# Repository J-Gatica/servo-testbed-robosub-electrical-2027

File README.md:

# Servo Testbed Project

Team members:
- Jayden
- Aleks
- Dwayne
- Cason

# Project Overview

Design and print a PCB to test the functionality of different types of servos for the SDSU Mechatronics Club during the 2026 Fall semester
- "create a pcb board that outputs a pwm signal that has .5-2.5ms high period (just like intro project) that is manually controlled by potentiometer"

PCB schematic and layout designed using KiCAD V10.0

MCU programmed using STM32CubeIDE in C

# Capabilities

- STM32F103C8T6 controlled

- Testing mode control:
  - Manual potentiometer sweep
  - Automatic sweep, potentiometer speed control
  - X degree step increment, potentiometer speed control
  - WIP
  
- 12V, 8.4V, 7.4V, 6V, 5V, 3V3 voltage outputs
  - 3/4 of each, two 12V outputs. 16/22 outputs total
  - reverse polarity protection up to (insert pmos ratings)

- Status display
  - Current draw
  - Expected output angle
  - Potentiometer angle
  - PWM data (duty cycle, frequency)

- 2 DC motor outputs
  - CAN control

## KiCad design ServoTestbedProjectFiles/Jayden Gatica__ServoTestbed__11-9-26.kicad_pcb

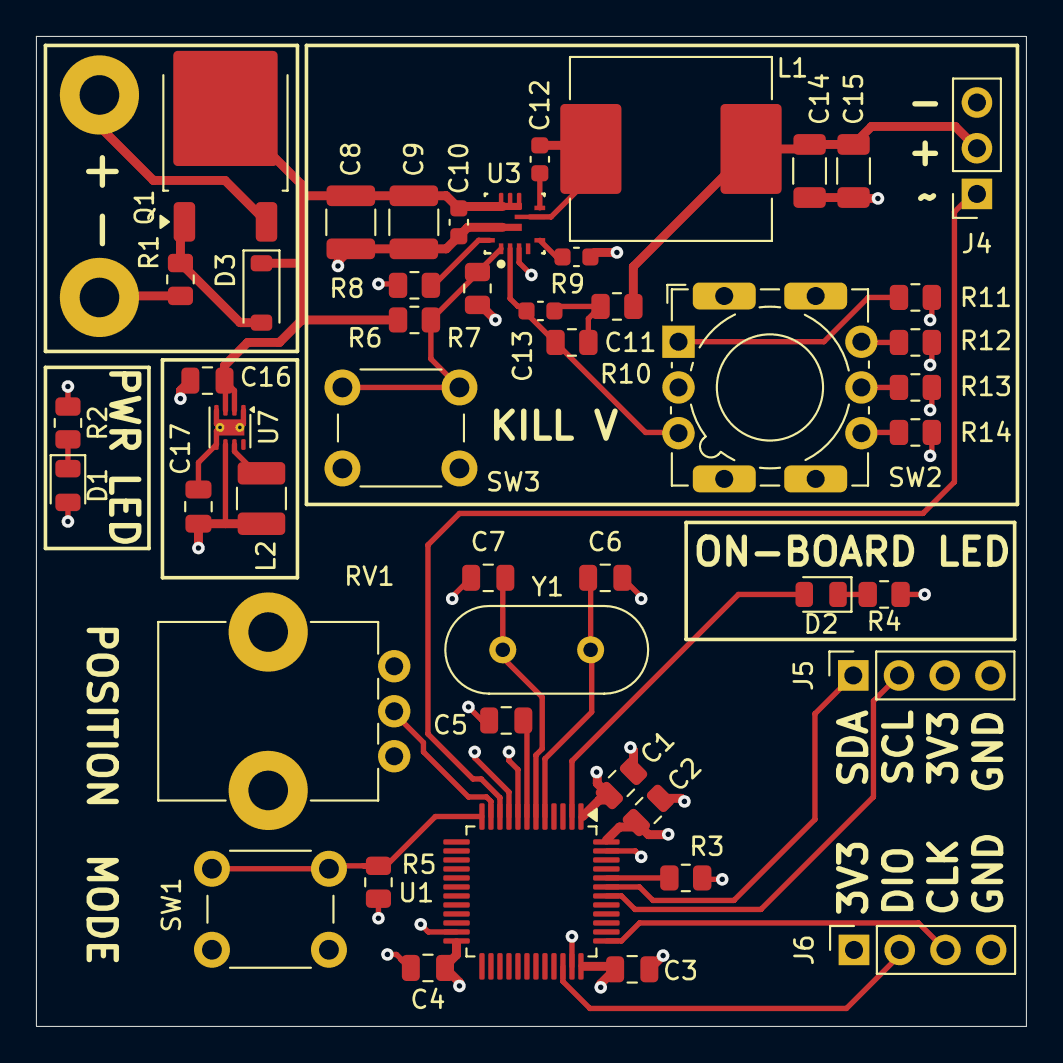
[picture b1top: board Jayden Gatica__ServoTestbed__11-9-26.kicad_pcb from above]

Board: 4 copper layers, 55.0 x 55.0 mm, 50 parts (0 on the bottom side), 32 nets.

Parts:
+: INPUT +15V; MountingHole_2.2mm_M2_Pad
-: INPUT GND; MountingHole_2.2mm_M2_Pad
C1, C2, C3, C4: 100nF; C_0805_2012Metric
C5: 100n; C_0805_2012Metric
C6: 30pF; C_0805_2012Metric
C7: 30Pf; C_0805_2012Metric
C8, C9: 10uF; C_1210_3225Metric
C10, C12: 0.1uF; C_0603_1608Metric
C11: 47nF; C_0603_1608Metric
C13: 150pF; C_0603_1608Metric
C14, C15: 22uF; C_1206_3216Metric
C16: 10uF; C_0805_2012Metric
C17: 22uF; C_0805_2012Metric
D1: PWR LED; LED_0805_2012Metric
D2: On-Board LED; LED_0805_2012Metric
D3: BZT52C12 - 12V; D_SOD-123
J4: 12V servo; PinSocket_1x03_P2.54mm_Vertical
J5: I2C display connector; PinSocket_1x04_P2.54mm_Vertical
J6: ST-link connector; PinSocket_1x04_P2.54mm_Vertical
L1: 5.6 uH; L_Bourns_SRP1050WA
L2: 2.2uH; L_1210_3225Metric
Q1: AO34185e; TO-252-2
R1: 100k; R_0805_2012Metric
R2, R4: 510R; R_0805_2012Metric
R3, R5: 10k; R_0805_2012Metric
R6: 169k; R_0805_2012Metric
R7: 36.1k; R_0805_2012Metric
R8: 52.3k; R_0805_2012Metric
R9: 49.9; R_0805_2012Metric
R10: 73.2K; R_0805_2012Metric
R11: 3.83k; R_0805_2012Metric
R12: 8.06k; R_0805_2012Metric
R13: 8.78k; R_0805_2012Metric
R14: 16.2k; R_0805_2012Metric
RV1: 10k; Potentiometer_Bourns_PTV09A-1_Single_Vertical
SW1, SW3: SW_Push; SW_PUSH_6mm
SW2: SW_Rotary_1x4_MP; SW_NKK_NR01
U1: STM32F103C8T6; LQFP-48_7x7mm_P0.5mm
U3: TPS56A37RPAR; RPA0010A-MFG
U7: TPS62162DSG; Texas_DSG0008A_WSON-8-1EP_2x2mm_P0.5mm_EP0.9x1.6mm_ThermalV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
Y1: 16MHz; Crystal_HC49-4H_Vertical

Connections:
3V3: C1.1, C2.1, C3.1, C4.1, C17.1, D1.2 (A), J5.3, J6.1, L2.2, RV1.3, SW1.2, U1.1 (VBAT), U1.9 (VDDA), U1.24 (VDD), U1.36 (VDD), U1.48 (VDD), U7.6 (VOS)
+15V_PROTECTED: C8.1, C9.1, C10.1, C16.1, D3.1 (K), Q1.2 (S), R6.1, U3.8 (VIN), U7.2 (VIN), U7.3 (EN)
+V buck output: C14.2, C15.1, J4.2, L1.2, R9.1
/BOOT0: R3.2, U1.44 (BOOT0)
/NRST: C5.2, U1.7 (NRST)
GND: -.1 (1_1), C1.2, C2.2, C3.2, C4.2, C5.1, C6.1, C7.1, C8.2, C9.2, C10.2, C11.2, C14.1, C15.2, C16.2, C17.2, J4.3, J5.4, J6.4, R1.2, R2.1, R3.1, R4.1, R5.2, R7.2, R8.2, R11.2, R12.2, R13.2, R14.2, RV1.1, SW2.MP, SW3.1, U1.8 (VSSA), U1.23 (VSS), U1.35 (VSS), U1.47 (VSS), U3.3 (AGND), U3.9 (PGND), U7.1 (PGND), U7.4 (AGND), U7.5 (FB), U7.9 (PAD)
unnamed: C13.1, R9.2, R10.1
unnamed: D1.1 (K), R2.2
unnamed: D2.2 (A), U1.2 (PC13)
unnamed: D2.1 (K), R4.2
unnamed: D3.2 (A), Q1.1 (G), R1.1
unnamed: +.1 (1_1), Q1.3 (D)
unnamed: R11.1, SW2.1
unnamed: R12.1, SW2.2
unnamed: R13.1, SW2.3
unnamed: R14.1, SW2.4
unnamed: RV1.2, U1.11 (PA1)
unnamed: R5.1, SW1.1, U1.12 (PA2)
unnamed: C6.2, U1.5 (PD0), Y1.2
unnamed: C7.2, U1.6 (PD1), Y1.1
unnamed: C12.1, U3.7 (BOOT)
unnamed: R6.2, R7.1, SW3.2, U3.1 (EN)
unnamed: C13.2, R10.2, SW2.5, U3.2 (FB)
unnamed: R8.1, U3.10 (MODE)
unnamed: C11.1, U3.5 (SS)
unnamed: C12.2, L1.1, U3.6 (SW)
unnamed: L2.1, U7.7 (SW)
SCL: J5.2, U1.42 (PB6)
SDA: J5.1, U1.43 (PB7)
SWCLK: J6.3, U1.37 (PA14)
SWDIO: J6.2, U1.34 (PA13)
ServoSignal: J4.1, U1.10 (PA0)
